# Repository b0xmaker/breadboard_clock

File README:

555 timer based clock with astable, monostable, and debounce between modes.

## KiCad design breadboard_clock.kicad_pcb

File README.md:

555 timer based clock with astable, monostable, and debounce between modes.

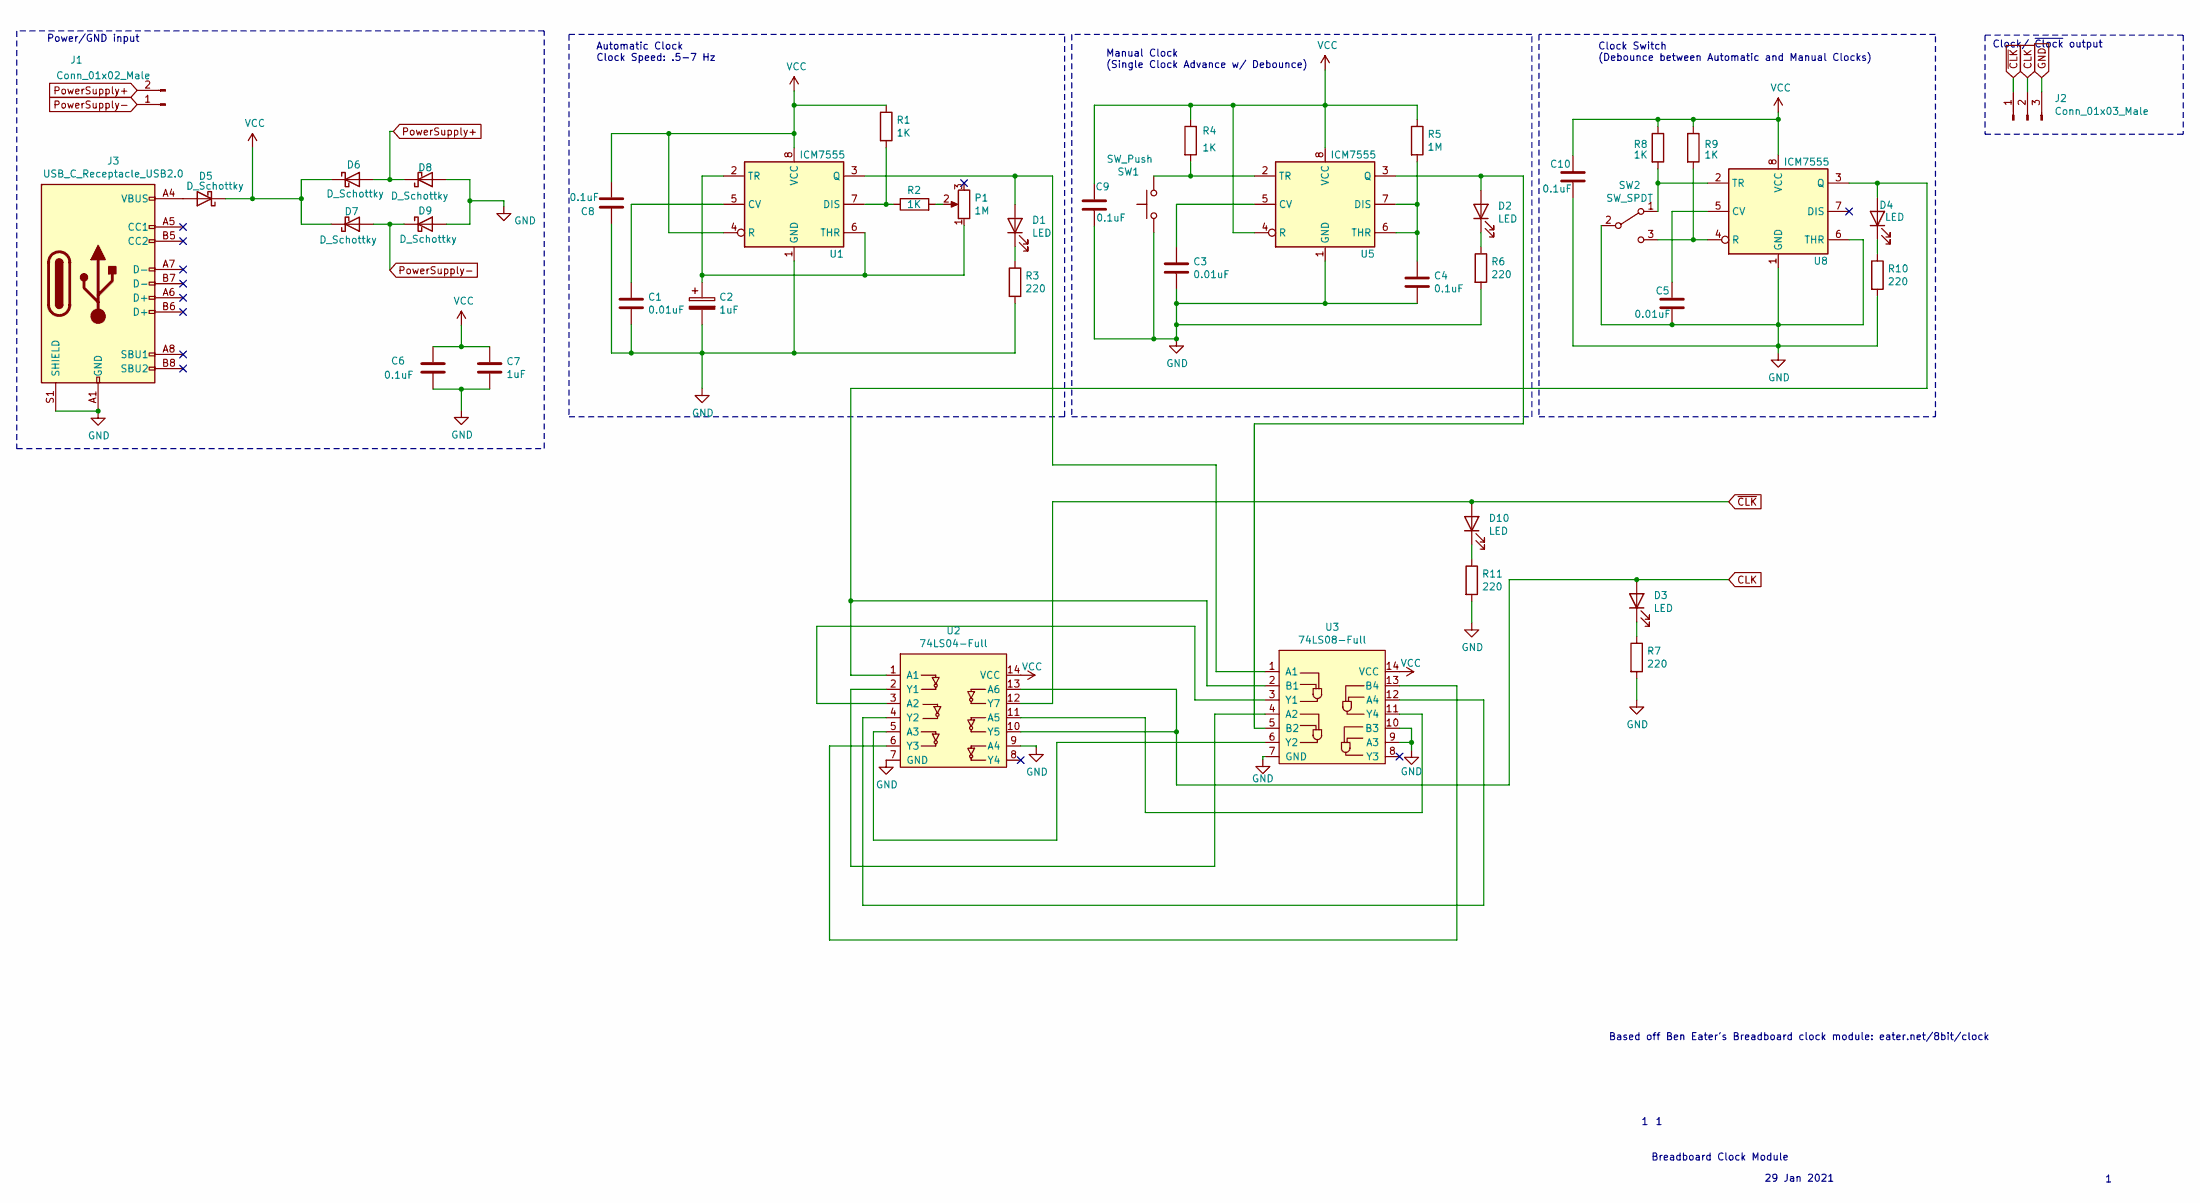
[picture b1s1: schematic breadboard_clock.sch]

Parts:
C1, C3, C5: 0.01uF; C_0805_2012Metric
C2, C7: 1uF; C_0805_2012Metric
C4, C6, C8, C9, C10: 0.1uF; C_0805_2012Metric
D1, D2, D3, D4, D10: LED; LED_0805_2012Metric
D5, D6, D7, D8, D9: D_Schottky; D_0805_2012Metric_Pad1.15x1.40mm_HandSolder
J1: Conn_01x02_Male; PinHeader_1x02_P2.54mm_Vertical_SMD_Pin1Right
J2: Conn_01x03_Male; PinHeader_1x03_P2.54mm_Vertical_SMD_Pin1Right
J3: USB_C_Receptacle_USB2.0; USB_C_Receptacle_Amphenol_12401610E4-2A
P1: 1M; Potentiometer_Bourns_3214J_Horizontal
R1, R2, R4, R8, R9: 1K; R_0805_2012Metric
R3, R6, R7, R10, R11: 220; R_0805_2012Metric
R5: 1M; R_0805_2012Metric
SW1: SW_Push; SW_SPST_B3U-1100P-B
SW2: SW_SPDT; SW_SPDT_PCM12
U1, U5, U8: ICM7555; SOIC-8_3.9x4.9mm_P1.27mm
U2: 74LS04-Full; SOIC-14_3.9x8.7mm_P1.27mm
U3: 74LS08-Full; SOIC-14_3.9x8.7mm_P1.27mm

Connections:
CLK: D3.2 (A), J2.2, U2.10 (Y5), U2.13 (A6)
GND: C1.2, C2.2, C3.2, C4.2, C5.2, C6.2, C7.2, C8.1, C9.2, C10.2, D8.2 (A), D9.2 (A), J2.3, J3.A1 (GND), J3.A12 (GND), J3.B1 (GND), J3.B12 (GND), J3.S1 (SHIELD), R3.2, R6.2, R7.2, R10.2, R11.2, SW1.1, SW2.2 (B), U1.1 (GND), U2.7 (GND), U2.9 (A4), U3.7 (GND), U3.9 (A3), U3.10 (B3), U5.1 (GND), U8.1 (GND), U8.6 (THR)
unnamed: C1.1, U1.5 (CV)
unnamed: C2.1, P1.1, U1.2 (TR), U1.6 (THR)
unnamed: C3.1, U5.5 (CV)
unnamed: C4.1, R5.2, U5.6 (THR), U5.7 (DIS)
unnamed: C5.1, U8.5 (CV)
unnamed: D1.1 (K), R3.1
unnamed: D1.2 (A), U1.3 (Q), U3.1 (A1)
unnamed: D2.1 (K), R6.1
unnamed: D2.2 (A), U3.5 (B2), U5.3 (Q)
unnamed: D3.1 (K), R7.1
unnamed: D4.1 (K), R10.1
unnamed: D4.2 (A), U2.1 (A1), U3.2 (B1), U8.3 (Q)
unnamed: D5.2 (A), J3.A4 (VBUS), J3.A9 (VBUS), J3.B4 (VBUS), J3.B9 (VBUS)
unnamed: D10.1 (K), R11.1
unnamed: P1.2, R2.2
unnamed: R1.2, R2.1, U1.7 (DIS)
unnamed: R4.2, SW1.2, U5.2 (TR)
unnamed: R8.2, SW2.1 (A), U8.2 (TR)
unnamed: R9.2, SW2.3 (C), U8.4 (R)
unnamed: U2.2 (Y1), U3.4 (A2)
unnamed: U2.3 (A2), U3.3 (Y1)
unnamed: U2.4 (Y2), U3.12 (A4)
unnamed: U2.5 (A3), U3.6 (Y2)
unnamed: U2.6 (Y3), U3.13 (B4)
unnamed: U2.11 (A5), U3.11 (Y4)
PowerSupply+: D6.2 (A), D8.1 (K), J1.2
PowerSupply-: D7.2 (A), D9.1 (K), J1.1
VCC: C6.1, C7.1, C8.2, C9.1, C10.1, D5.1 (K), D6.1 (K), D7.1 (K), R1.1, R4.1, R5.1, R8.1, R9.1, U1.4 (R), U1.8 (VCC), U2.14 (VCC), U3.14 (VCC), U5.4 (R), U5.8 (VCC), U8.8 (VCC)
~CLK: D10.2 (A), J2.1, U2.12 (Y7)

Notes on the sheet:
Breadboard Clock Module
29 Jan 2021
Based off Ben Eater's Breadboard clock module: eater.net/8bit/clock
Power/GND input
Manual Clock (Single Clock Advance w/ Debounce)
Clock Switch (Debounce between Automatic and Manual Clocks)
Automatic Clock Clock Speed: .5-7 Hz
Clock/ ~Clock output

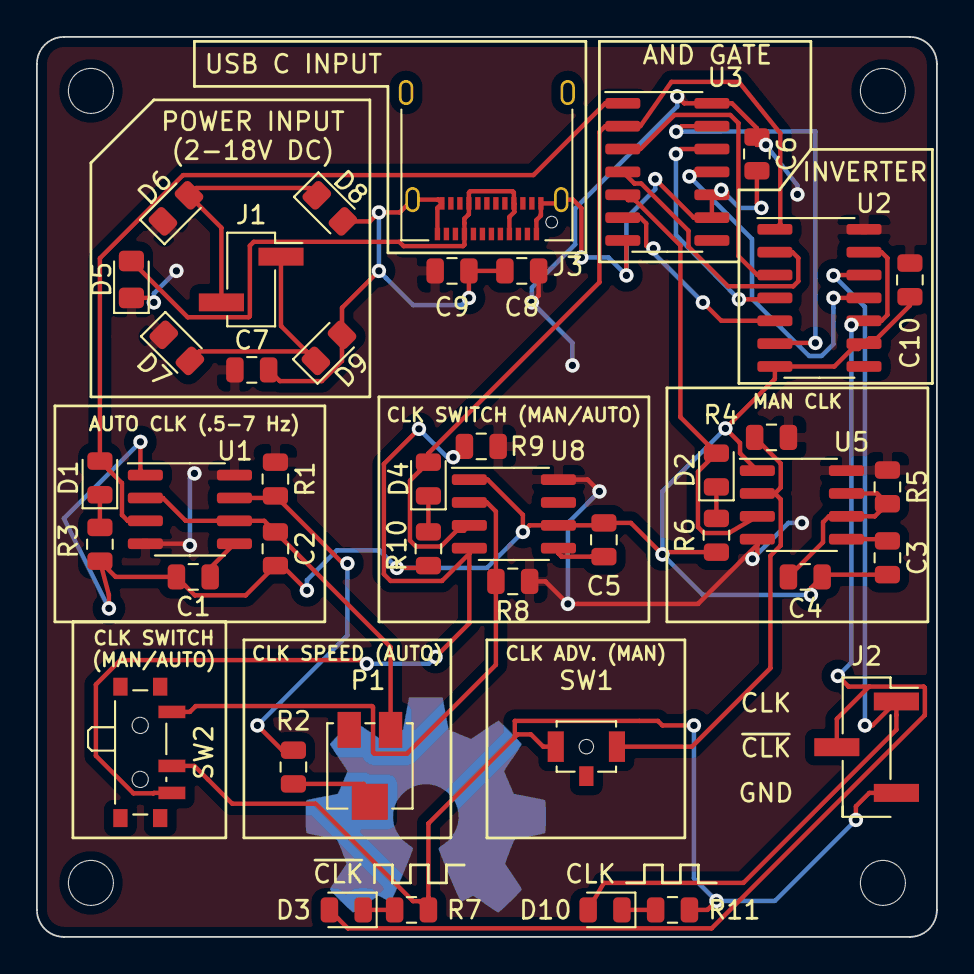
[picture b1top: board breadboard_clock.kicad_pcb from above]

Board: 2 copper layers, 50.0 x 50.0 mm, 42 parts (0 on the bottom side), 31 nets.

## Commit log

2021-01-31 updated schematic, adding SPDT switch for potential "turbo" mode
2021-03-06 Create datasheets
2021-03-21 commit from terminal
2021-03-21 adding README
2021-03-21 Create TODO
2021-03-21 Update TODO
2021-03-21 working version
2021-07-09 Add files via upload
    Modified PCB/Schematic to get clock switching 555 circuit working. Trace was leading from pin 4 to GND, causing this 555 to always be in "reset" mode.
2021-11-19 Rename README to README.md
